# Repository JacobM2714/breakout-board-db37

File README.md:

# breakout-board-db37
PCB that breaks out 32 signals across 2 DB37 connectors and fits within a 2U space

Digikey links:

Proposed DB37 Male Connector:
https://www.digikey.com/en/products/detail/te-connectivity-amp-connectors/2301836-1/7776540

Proposed Coaxial Connector (BNC):
https://www.digikey.com/en/products/detail/te-connectivity-amp-connectors/1274571-1/691546

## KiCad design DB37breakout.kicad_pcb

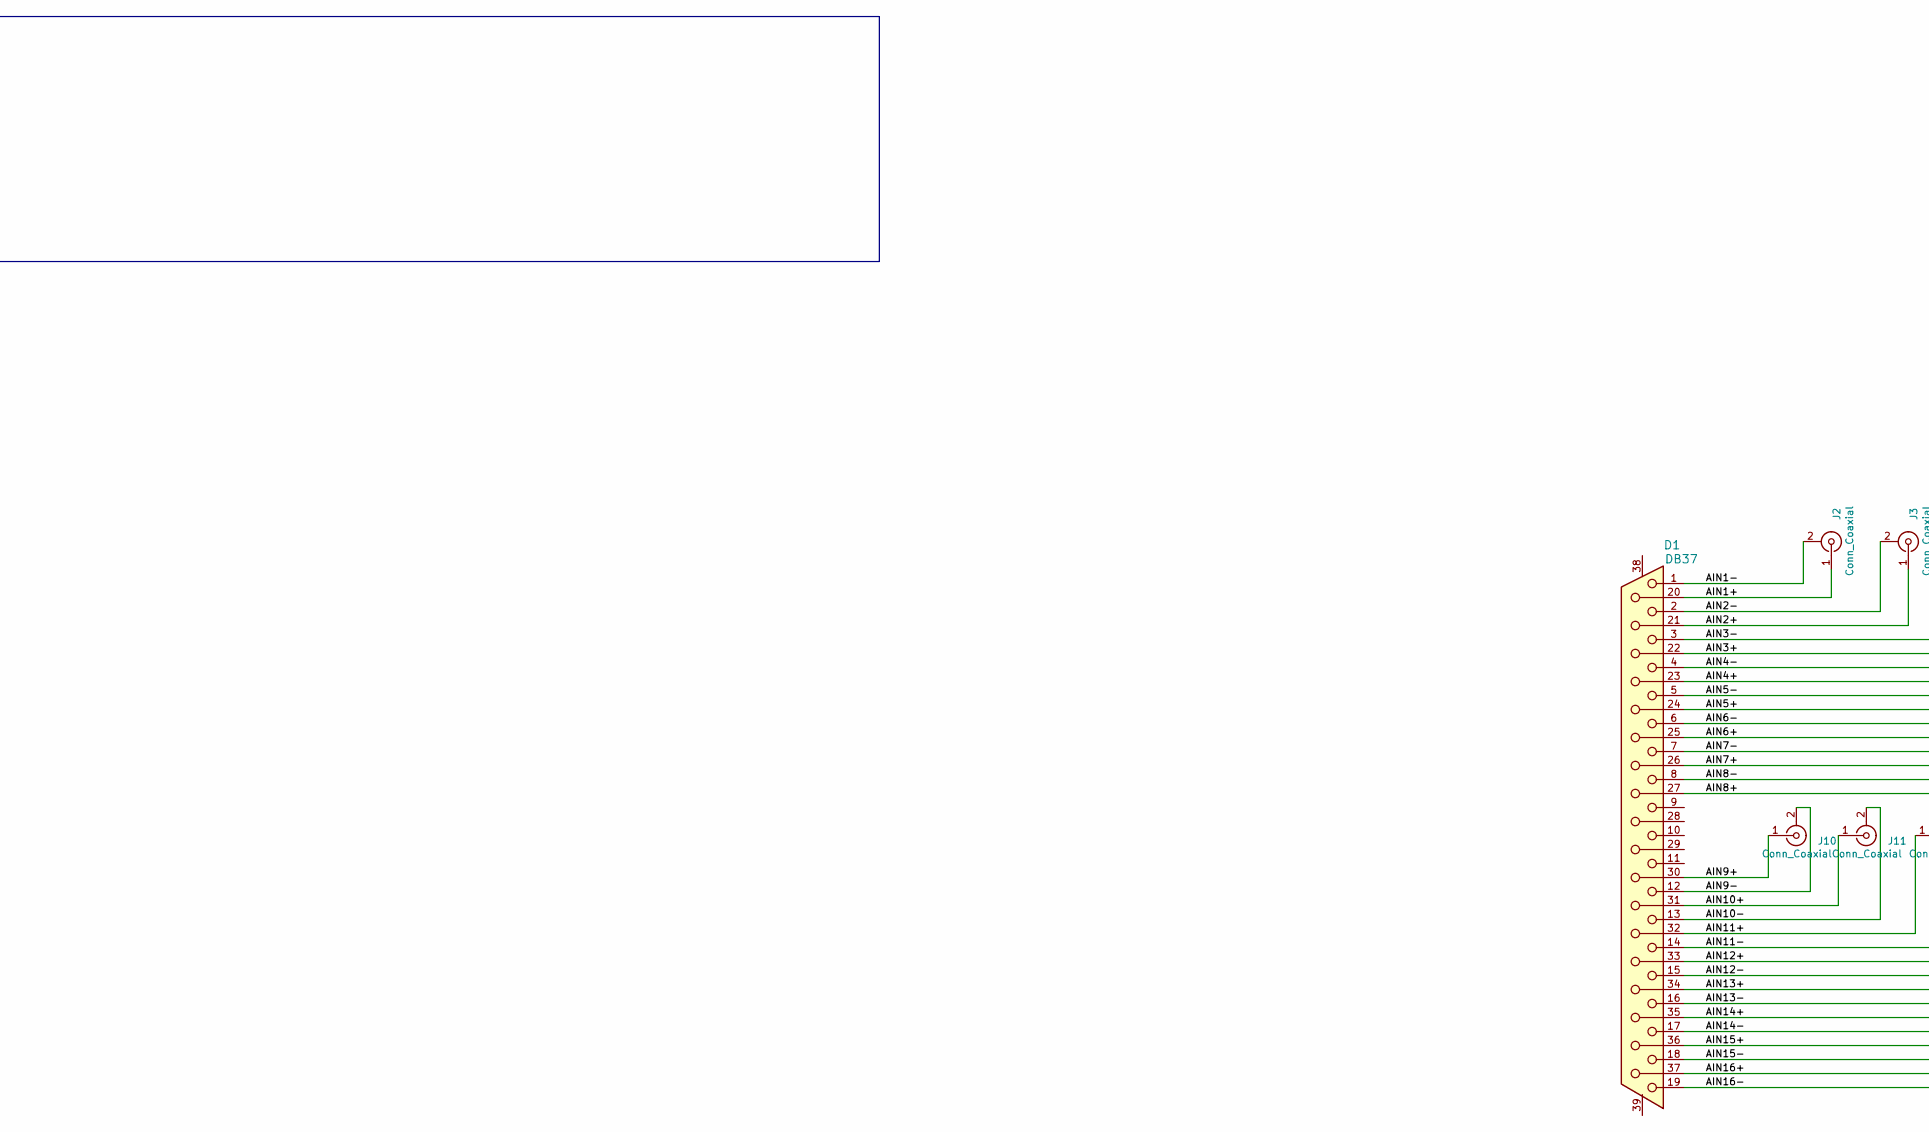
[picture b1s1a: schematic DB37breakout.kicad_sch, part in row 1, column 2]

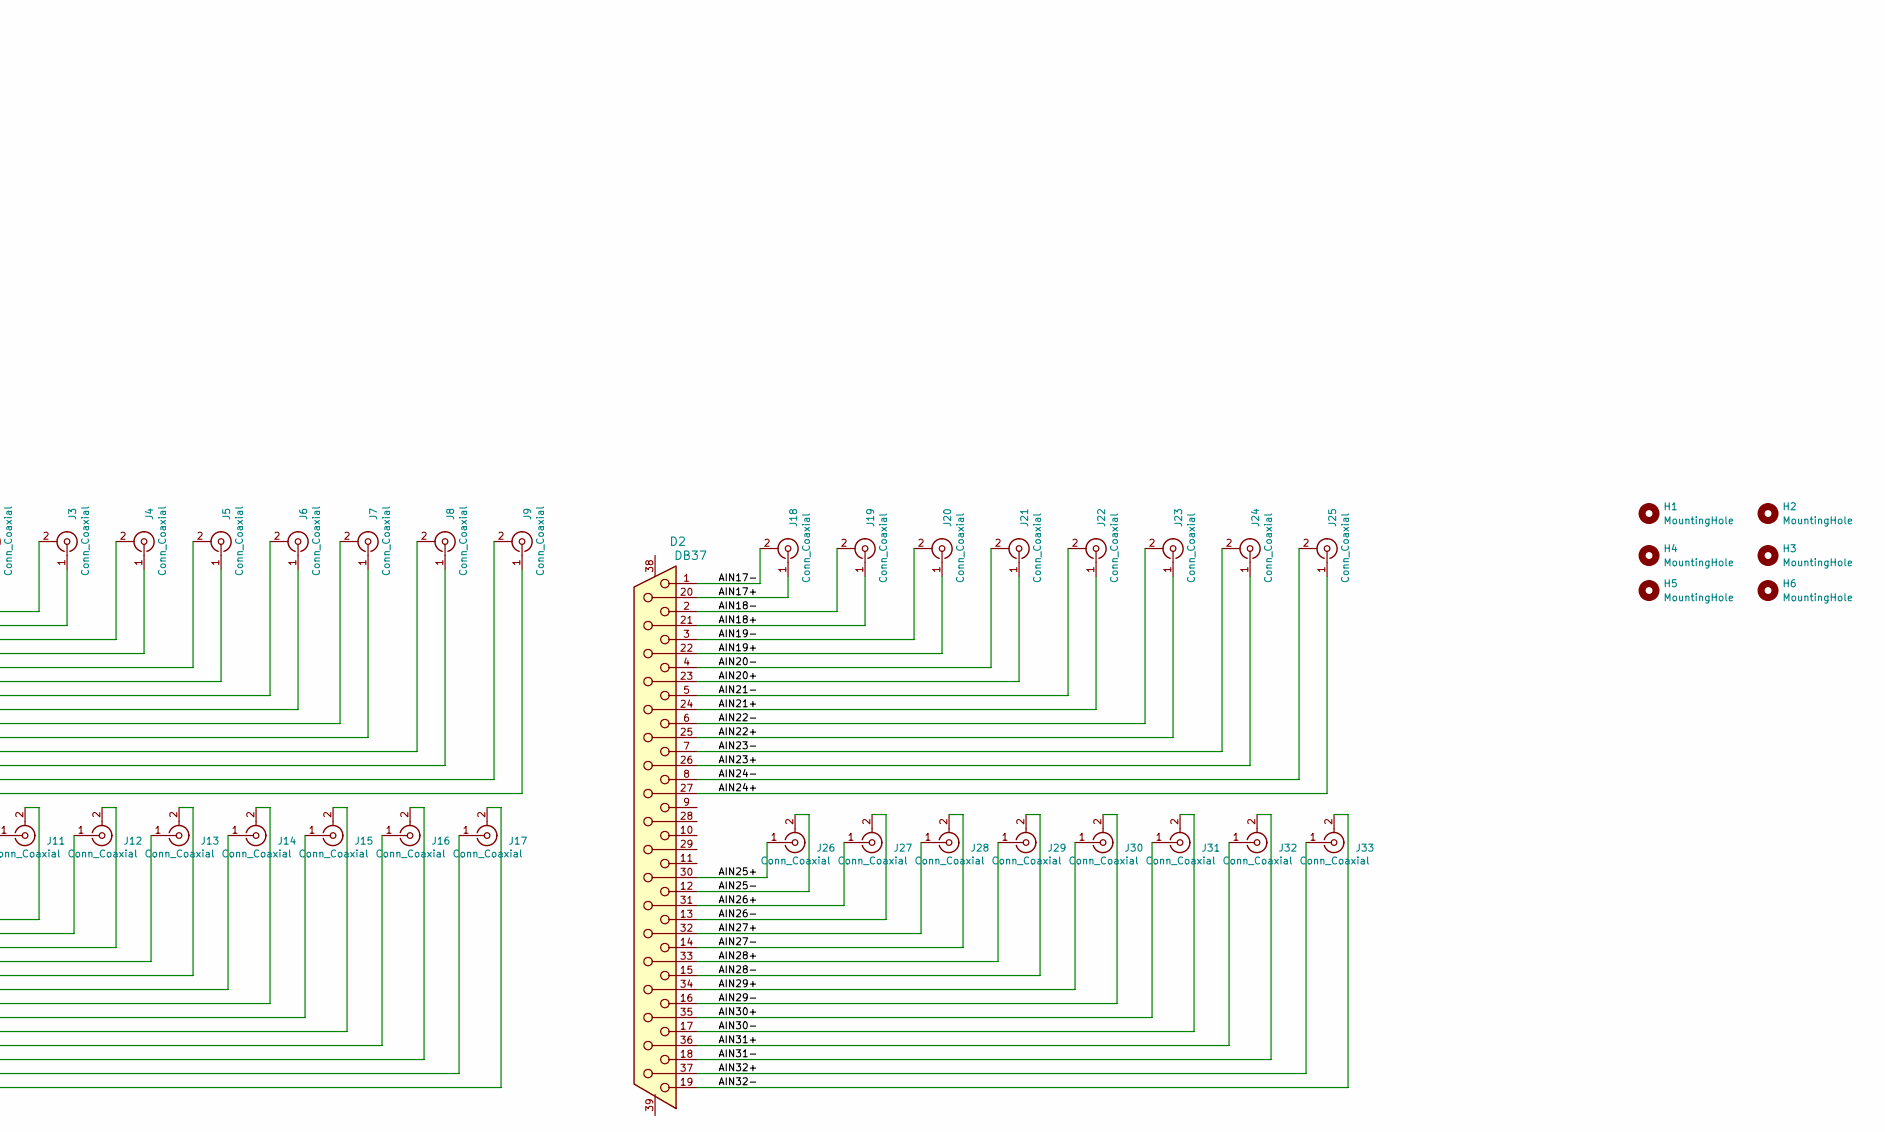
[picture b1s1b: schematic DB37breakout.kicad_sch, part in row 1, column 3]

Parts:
D1, D2: DB37; DSUB-37_Pins_Vertical_P2.77x2.84mm_MountingHoles; MPN 5747847-6
H1, H2, H3, H4, H5, H6: MountingHole; MountingHole_3mm
J2, J3, J4, J5, J6, J7, J8, J9, J10, J11, J12, J13, J14, J15, J16, J17, J18, J19, J20, J21, J22, J23, J24, J25, J26, J27, J28, J29, J30, J31, J32, J33: Conn_Coaxial; BNC_TEConnectivity_1478204_Vertical

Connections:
/AIN1+: D1.20, J2.1 (In)
/AIN1-: D1.1, J2.2 (Ext)
/AIN2+: D1.21, J3.1 (In)
/AIN2-: D1.2, J3.2 (Ext)
/AIN3+: D1.22, J4.1 (In)
/AIN3-: D1.3, J4.2 (Ext)
/AIN4+: D1.23, J5.1 (In)
/AIN4-: D1.4, J5.2 (Ext)
/AIN5+: D1.24, J6.1 (In)
/AIN5-: D1.5, J6.2 (Ext)
/AIN6+: D1.25, J7.1 (In)
/AIN6-: D1.6, J7.2 (Ext)
/AIN7+: D1.26, J8.1 (In)
/AIN7-: D1.7, J8.2 (Ext)
/AIN8+: D1.27, J9.1 (In)
/AIN8-: D1.8, J9.2 (Ext)
/AIN9+: D1.30, J10.1 (In)
/AIN9-: D1.12, J10.2 (Ext)
/AIN10+: D1.31, J11.1 (In)
/AIN10-: D1.13, J11.2 (Ext)
/AIN11+: D1.32, J12.1 (In)
/AIN11-: D1.14, J12.2 (Ext)
/AIN12+: D1.33, J13.1 (In)
/AIN12-: D1.15, J13.2 (Ext)
/AIN13+: D1.34, J14.1 (In)
/AIN13-: D1.16, J14.2 (Ext)
/AIN14+: D1.35, J15.1 (In)
/AIN14-: D1.17, J15.2 (Ext)
/AIN15+: D1.36, J16.1 (In)
/AIN15-: D1.18, J16.2 (Ext)
/AIN16+: D1.37, J17.1 (In)
/AIN16-: D1.19, J17.2 (Ext)
/AIN17+: D2.20, J18.1 (In)
/AIN17-: D2.1, J18.2 (Ext)
/AIN18+: D2.21, J19.1 (In)
/AIN18-: D2.2, J19.2 (Ext)
/AIN19+: D2.22, J20.1 (In)
/AIN19-: D2.3, J20.2 (Ext)
/AIN20+: D2.23, J21.1 (In)
/AIN20-: D2.4, J21.2 (Ext)
/AIN21+: D2.24, J22.1 (In)
/AIN21-: D2.5, J22.2 (Ext)
/AIN22+: D2.25, J23.1 (In)
/AIN22-: D2.6, J23.2 (Ext)
/AIN23+: D2.26, J24.1 (In)
/AIN23-: D2.7, J24.2 (Ext)
/AIN24+: D2.27, J25.1 (In)
/AIN24-: D2.8, J25.2 (Ext)
/AIN25+: D2.30, J26.1 (In)
/AIN25-: D2.12, J26.2 (Ext)
/AIN26+: D2.31, J27.1 (In)
/AIN26-: D2.13, J27.2 (Ext)
/AIN27+: D2.32, J28.1 (In)
/AIN27-: D2.14, J28.2 (Ext)
/AIN28+: D2.33, J29.1 (In)
/AIN28-: D2.15, J29.2 (Ext)
/AIN29+: D2.34, J30.1 (In)
/AIN29-: D2.16, J30.2 (Ext)
/AIN30+: D2.35, J31.1 (In)
/AIN30-: D2.17, J31.2 (Ext)
/AIN31+: D2.36, J32.1 (In)
/AIN31-: D2.18, J32.2 (Ext)
/AIN32+: D2.37, J33.1 (In)
/AIN32-: D2.19, J33.2 (Ext)

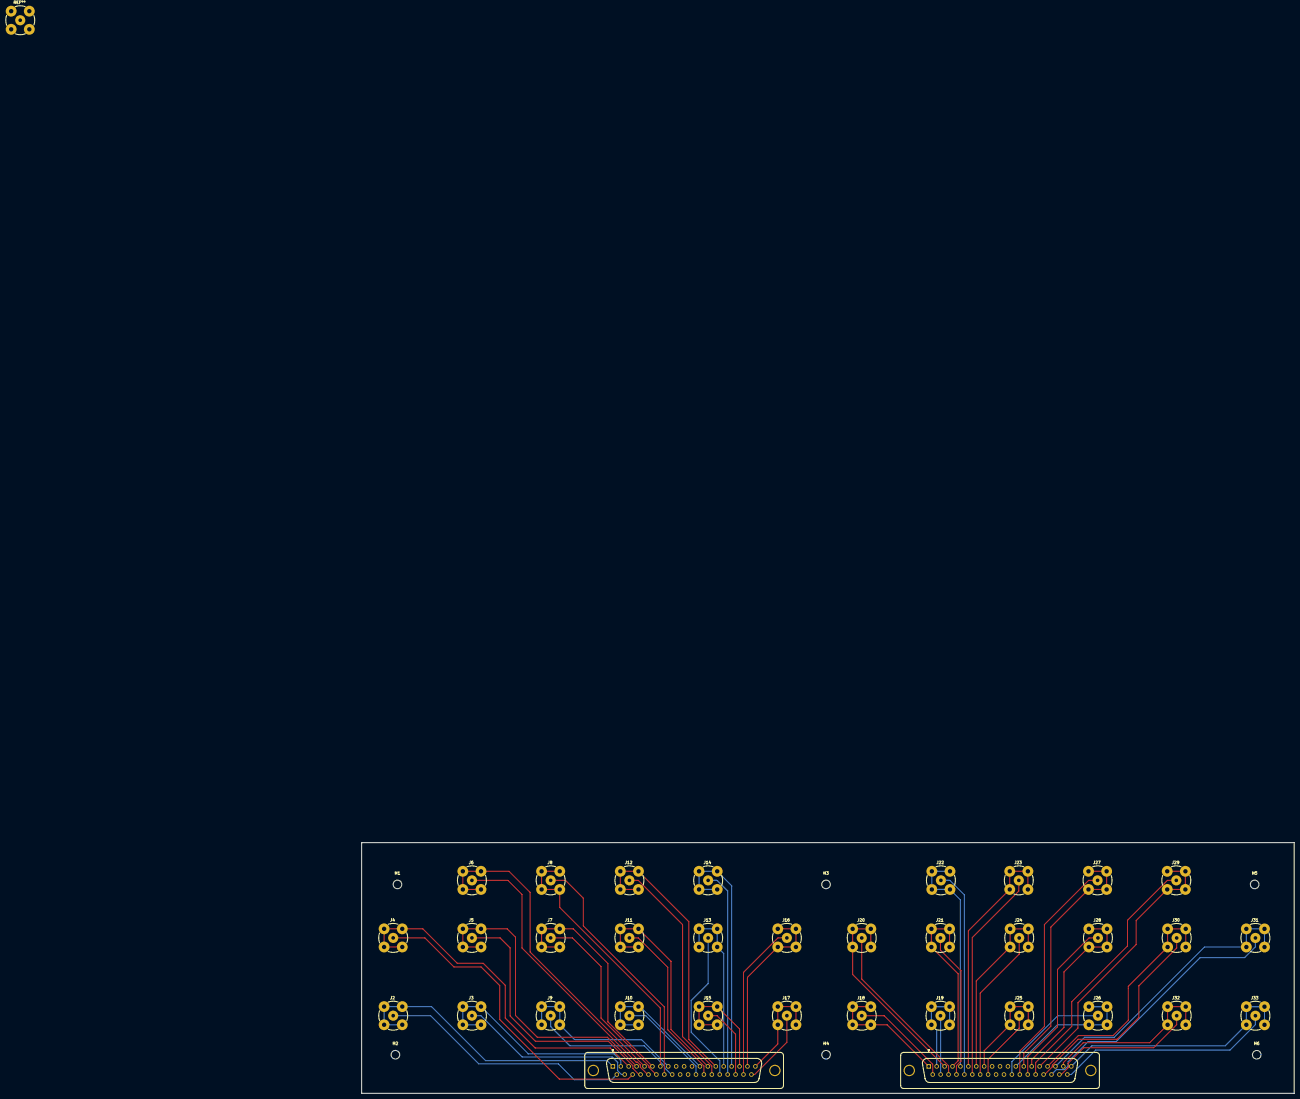
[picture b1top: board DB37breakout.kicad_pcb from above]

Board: 2 copper layers, 326.2 x 87.7 mm, 40 parts (0 on the bottom side), 64 nets.

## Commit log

2025-12-28 Adjusted paper size inn schematic and PCB editors
    Adjusted paper size inn schematic and PCB editors
2026-01-03 Changed BNC footprint to vertical Through Hole; redesigned board with greater space between traces and footprints; shortened board length and expanded board width to lightly less than a 2U space
2026-01-03 connected unconnected traces
